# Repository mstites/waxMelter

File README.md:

# waxMelter
Custom designed board and software for a bangbang controlled thermocouple feedback wax melter. Please see [project page](https://www.mstites.com/items/wax_melter.html) for more information.

## Overview
The board heats and maintains the temperature of a container of candle wax via controlling a hot plate with a relay power control. All code was written in C in an Arduino based environment for an Adafruit ESP32 Huzzah. There is a fully functional OLED and button UI and web based UI.

## Files and Notes
* For final software iteration please see [software/dualUi](software/dualUi). Software depends on the [espressif-esp32](https://github.com/espressif/arduino-esp32#using-through-arduino-ide) and [ESPAsyncWebServer](https://github.com/me-no-dev/ESPAsyncWebServer) libraries. Any other missing dependencies should be able to be installed through the Arduino IDE (eg [Button2](https://github.com/LennartHennigs/Button2), [RunningMedian](https://github.com/RobTillaart/RunningMedian)).
* Project proposal is located in [proposal](proposal). This was a project for [ENGR3499-02: Microcontrollers for the Real World](http://reifel.org/realworld/) taught by Stan Reifel at Olin College of engineering. Though this project was also a passion work as I [make many candles](http://trandleboutique.com).
* Final schematic, kicad files, and PCB files are located in [schematic](schematic). It should be noted that the final PCB I ended up with I had to make adjustments to. I had to disconnect the A1 to SENSOR_0 connection and reconnect SENSOR_0 to A2. The same would also have to be done with respect to A5 and SENSOR_1 (to some ADC1 pin). This is because the original pins, A1 and A5, I picked are connected to ADC2 on the ESP. Only ADC1 can be used while wifi is enabled ([see here for pin numbering](https://learn.adafruit.com/adafruit-huzzah32-esp32-feather/pinouts)).

## Parts List
* [Adafruit HUZZAH32](https://www.adafruit.com/product/3591)
* [Thermocouple Amplifier AD8495](https://www.adafruit.com/product/1778)
* [K Type Thermocouple](https://www.ebay.com/itm/1M-K-Type-Thermocouple-Sensor-Digital-Thermometer-Temperature-Meter-TK80-4JPL8/282896189061?_trkparms=ispr%3D1&hash=item41dded4685:g:auQAAOSwikdau~0I&amdata=enc%3AAQAFAAACYBaobrjLl8XobRIiIML1V4Imu%252Fn%252BzU5L90Z278x5ickk7PdDazAlGltMLJlUhrWsD4ypBzXDBrr3EGbvDCD%252BOTfiTG%252FV6xARDfS6DhxpOawtq0wAUHwzCXVNlrquDkax%252BHLcfCpjODsCClfysZNmLcjKNhUCyZwlivq7Ou%252BSmp%252FNan3zi86bNOppmqGIBMdWiTFE6aq0N55rJ5p610VKqpsEUguP16E0hxd5inmBD20248dYwxENTtrZPJzbteu98xpsFoA6NRRONNO8AFAXX89%252FktMA%252FMYhMde28GDtzsb4Q%252FstK%252BytZGRtmxx2GJeJIjNEnUTIb2ZtmPVtaehLIrKyByYNRhgJ3trD8Uzl1OL1G6Ov1BHTu3ct5z6%252BYjT5Gn1gHn1WTkyAUGmD96HCcMx2kF4PVEo171c0GnQmpCPSK%252Ba1t5ZcDgoZA4wjEhZSgphf9bAZoL%252BTzL9r2Q1FGZkeqwcEwrHTXMSumlt%252FEBQSmBNDBf%252BVZwOZV1DEa5zsk8uRSAahogXBhsBiTncrrOCZMk1M%252Fb6JNapN67fctFa4vXdXtx75DZtH7jcddYi4seuXT9uvLQ%252BGizccfA5TaPQpMoAGivS1TTwWy26Bz2oLF4qjKl8lhn9gjkRAodJqWBnukNI%252BdxfboGJRnL1tupUHN1vHOuuQglrpdetpjcCG2atFgNjEhzRBVdqyXI5UYWCN3p%252FCElSElYjv48XtG05oh%252F%252F0i%252BNC37r2TF%252BFe4q4%252FOPX%252BPEo%252BL9JVKTemFHr%252BIyor4iOTMGOTiiJJ6U9t5zFFEMdbP8pcCW20AqyD6I7%7Ccksum%3A282896189061fe03b50efa204da1abdccf1154f0cbb6%7Campid%3APL_CLK%7Cclp%3A2334524)
* [Hot Plate](https://www.amazon.com/gp/product/B07MMT2SC5/ref=ask_ql_qh_dp_hza)
* [Outlet Power Relay](https://www.amazon.com/Iot-Relay-Enclosed-High-Power-Raspberry/dp/B00WV7GMA2/ref=sr_1_2?dchild=1&keywords=outlet+power+relay&qid=1601856536&sr=8-2)
* [SPI OLED 128x64](https://www.amazon.com/UCTRONICS-SSD1306-Self-Luminous-Display-Raspberry/dp/B072Q2X2LL/ref=sr_1_3?dchild=1&keywords=oled+display+arduino&qid=1602386754&sr=8-3)
* SPST Switch x6
* USB Power Supply
* Micro USB Cable
* LD1117V33 x2	
* 0.1uF Cermic Capacitor x6
* 10uF Electrolytic Capacitor x4
* 4.7K Resistor 1/8W x6
* 2 Pin Screw Terminal x2
Sockets:
* 16 pin x2
* 12 pin x2
* 4 pin x2

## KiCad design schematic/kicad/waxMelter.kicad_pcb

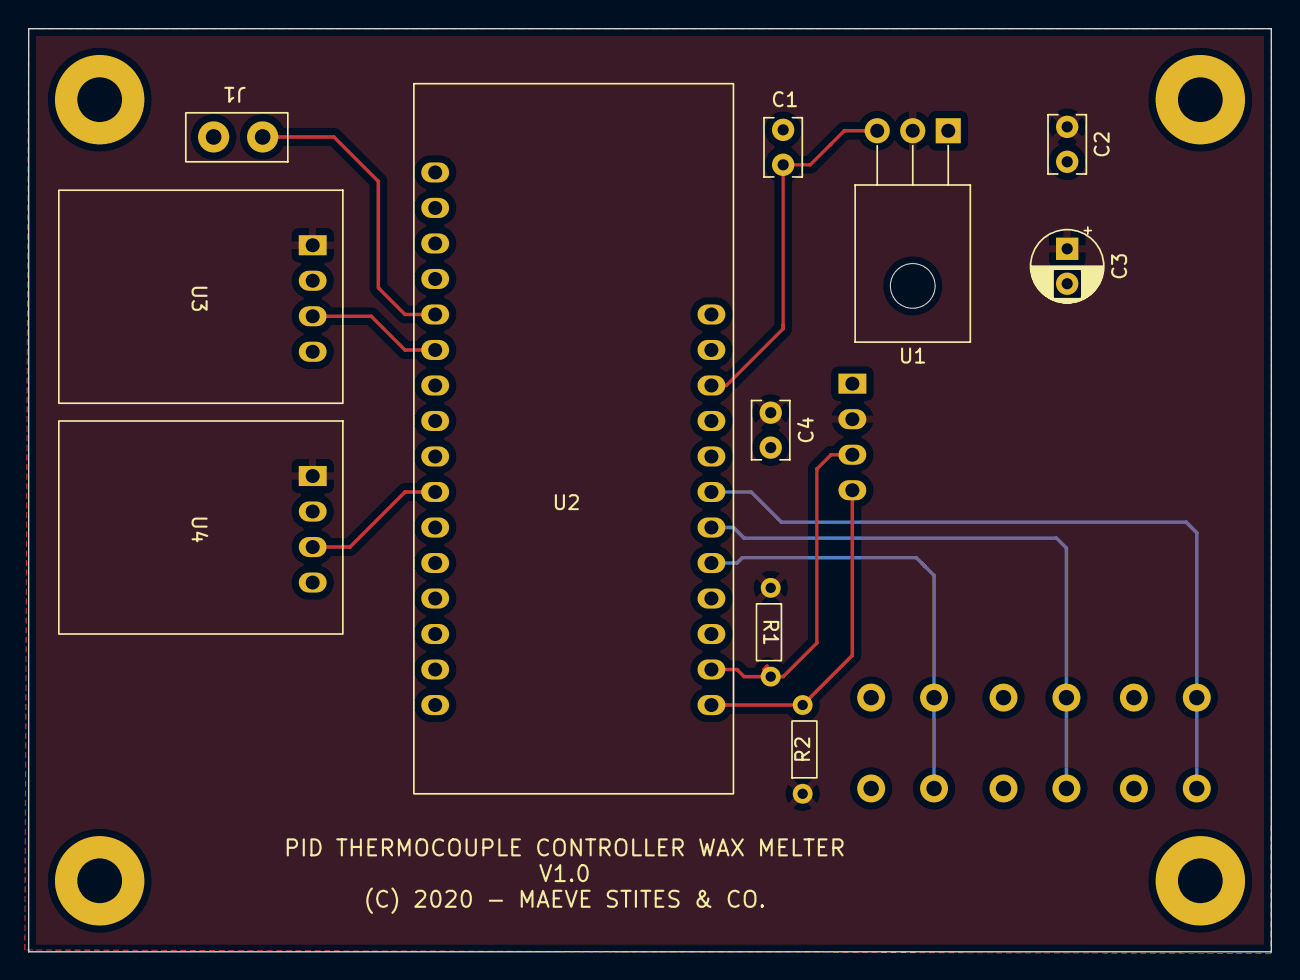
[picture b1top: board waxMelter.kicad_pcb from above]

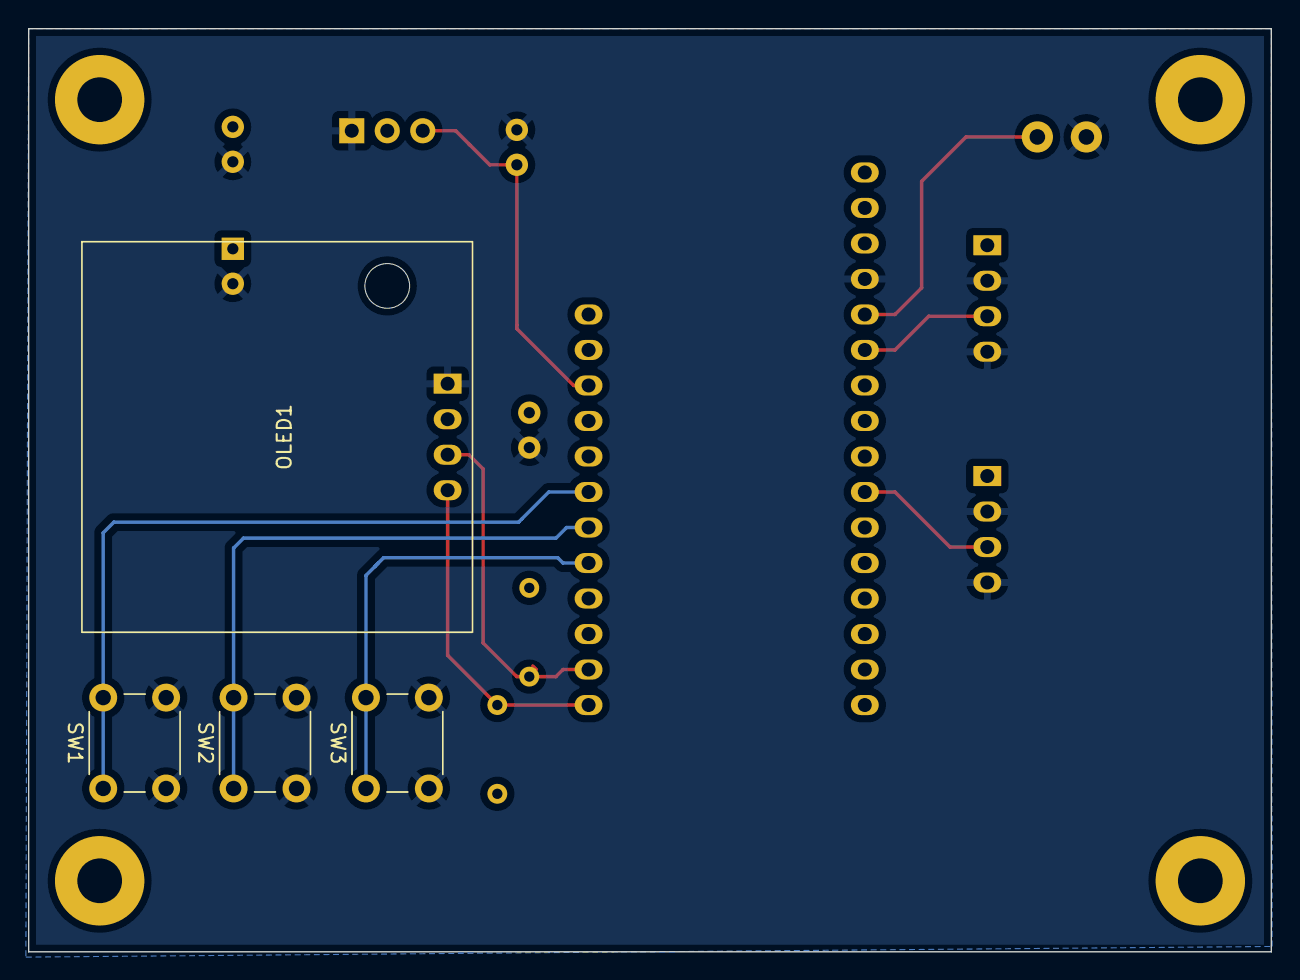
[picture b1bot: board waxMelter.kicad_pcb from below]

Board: 2 copper layers, 88.9 x 66.0 mm, 15 parts (4 on the bottom side), 11 nets.

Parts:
C1, C2, C4: 0.1uF; C_Rect_L4.0mm_W2.5mm_P2.50mm
C3: 10uF; CP_Radial_D5.0mm_P2.50mm
J1: Relay_Control_Terminal; 2PIN_SCREW
OLED1: .96_OLED; OLED
R1, R2: 4.7K; resistor 1-8
SW1: PWR; SW_PUSH_6mm
SW2: T+; SW_PUSH_6mm
SW3: T-; SW_PUSH_6mm
U1: LD1117V33; TO-126-3_Horizontal_TabDown
U2: HUZZAH32_ESP32; HUZZAH_ESP32
U3, U4: AD8495_Breakout; AD8495_amplifier

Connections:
+3V3: C2.1, C3.1, C4.2, OLED1.2 (VCC), R1.1, R2.1, U1.2 (VO), U3.1 (V+), U4.1 (V+)
+5V: C1.2, U1.3 (VI), U2.3 (USB)
GND: C1.1, C2.2, C3.2, C4.1, J1.2, OLED1.1 (GND), SW1.2, SW2.2, SW3.2, U1.1 (GND), U2.16 (GND), U3.2 (GND), U3.4 (GND), U4.2 (GND), U4.4 (GND)
I2C_SCL: OLED1.3 (SCL), R1.2, U2.11 (SCL)
I2C_SDA: OLED1.4 (SDA), R2.2, U2.12 (SDA)
unnamed: SW1.1, U2.6 (A10/GPIO27)
unnamed: SW2.1, U2.7 (A9/GPIO33/32K)
unnamed: SW3.1, U2.8 (A8/GPIO15)
OUTLET_CTRL: J1.1, U2.17 (A0/GPIO26)
SENSOR_0: U2.18 (A1/GPIO25), U3.3 (OUT)
SENSOR_1: U2.22 (A5/GPIO4), U4.3 (OUT)

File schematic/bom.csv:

Reference,Qnty, Value, Datasheet, Vendor Value
"C1, C2, C4",3,0.1uF,https://www.vishay.com/docs/45171/kseries.pdf,DK: BC1084CT-ND
C3,1,10uF,https://katalog.we-online.de/pbs/datasheet/860020572003.pdf,DK: 732-8937-1-ND
J1,1,Screw_Terminal_01x02,https://media.digikey.com/PDF/Data%20Sheets/Phoenix%20Contac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,DK: 277-5719-ND
OLED1,1,.96_OLED,https://cdn-shop.adafruit.com/datasheets/SSD1306.pdf,Amazon
"R1, R2",2,4.7K,https://www.seielect.com/catalog/sei-cf_cfm.pdf,DK: CF18JT4K70CT-ND
SW1,1,PWR,https://media.digikey.com/pdf/Data%20Sheets/APEM%20Component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,DK: 679-2428-ND
SW2,1,T+,https://media.digikey.com/pdf/Data%20Sheets/APEM%20Component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,DK: 679-2428-ND
SW3,1,T-,https://media.digikey.com/pdf/Data%20Sheets/APEM%20Component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,DK: 679-2428-ND
"TC1, TC2",2,Thermocouple,K Type Thermocouple,"Ebay, Amazon"
U1,1,LD1117V33,http://www.st.com/st-web-ui/static/active/en/resource/techni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,DK: 497-1491-5-ND
U2,1,HUZZAH32_ESP32,https://cdn-learn.adafruit.com/downloads/pdf/adafruit-huzzah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,Adafruit: 3591
"U3, U4",2,AD8495_Breakout,https://www.adafruit.com/product/1778,Adafruit: 1778

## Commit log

2020-11-01 Add proposal items into readme
2020-11-01 Upload most recent version of proposal from local drive
2020-11-01 Add schematic documentation
2020-11-01 Add kicad information
2020-11-02 Add testing notes
2020-11-02 Add web server examples
2020-11-02 Move testing.md to folder
2020-11-02 Remove duplicate webControl
2020-11-02 Add to do list
2020-11-02 Fix incorrect header type
2020-11-02 Add new example
2020-11-02 Update cam information
2020-11-19 hello world
2020-11-19 Remove unnecessary reset pin
2020-11-19 Add line by line template with colors
2020-11-19 Basic button functionality test
2020-11-19 Start experimentation with button2 package for button management
2020-11-19 Update notes to include button updates
2020-11-19 Clean up codee for specific use case
2020-11-19 Clean up unnecessary notes
2020-11-19 Add OLED notes
2020-11-19 Complete relay test code
2020-11-19 Complete temperature testing
2020-11-29 Add basic OLED display
2020-11-29 Add basic oled selection code
2020-11-29 Add selection control with buttons
2020-11-29 Add scaffolding for rest of code
2020-12-02 Add basic temp target control
2020-12-02 Reduce startup delay
2020-12-02 Organize calls
2020-12-02 Add heating page
2020-12-02 Simplify selection options
2020-12-02 Add live temperature reporting
2020-12-02 Reduce unnecessary refreshing
2020-12-02 Add relay control
2020-12-02 Fix current temp refresh
2020-12-09 Line up comments
2020-12-09 Change global variable names to camel case
2020-12-09 Add field basic code
2020-12-09 Find better starter code
2020-12-09 Set basic format
2020-12-09 Cut down to just one input field
2020-12-09 Start combination of all items
2020-12-09 Add functionality to fully update targetTemp
2020-12-09 Update heating base on slider result
2020-12-10 Add Stan's suggestions
2020-12-12 Functionize web startup
2020-12-12 Finish cleaning code for combination with dualUI code
2020-12-12 Add basic web ui
2020-12-12 Sync between dual UIs
2020-12-12 Update html style
2020-12-13 Add calibration data
2020-12-13 Move old testing files into testing folder
2020-12-13 Move calibration data to software dir
2020-12-13 Update schematic to match kicad
2020-12-13 Add new calibration curve
2020-12-13 Remove unnecessary comments
2020-12-15 Set adjusted pins post board refresh
2020-12-15 Increase oled update frequency when within 5 degrees
2020-12-15 Fix syntax error
2020-12-15 Clean up comments and code
2020-12-15 Add website link
2020-12-15 Add files and notes section
2020-12-15 fix trandleboutique link
2020-12-15 Add recommended schematic with notes on what happened
2020-12-17 Add schematic recommended
2020-12-17 Add updated kicad files

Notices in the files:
schematic/kicad/waxMelter.kicad_pcb:
(C) 2020 - MAEVE STITES & CO.
